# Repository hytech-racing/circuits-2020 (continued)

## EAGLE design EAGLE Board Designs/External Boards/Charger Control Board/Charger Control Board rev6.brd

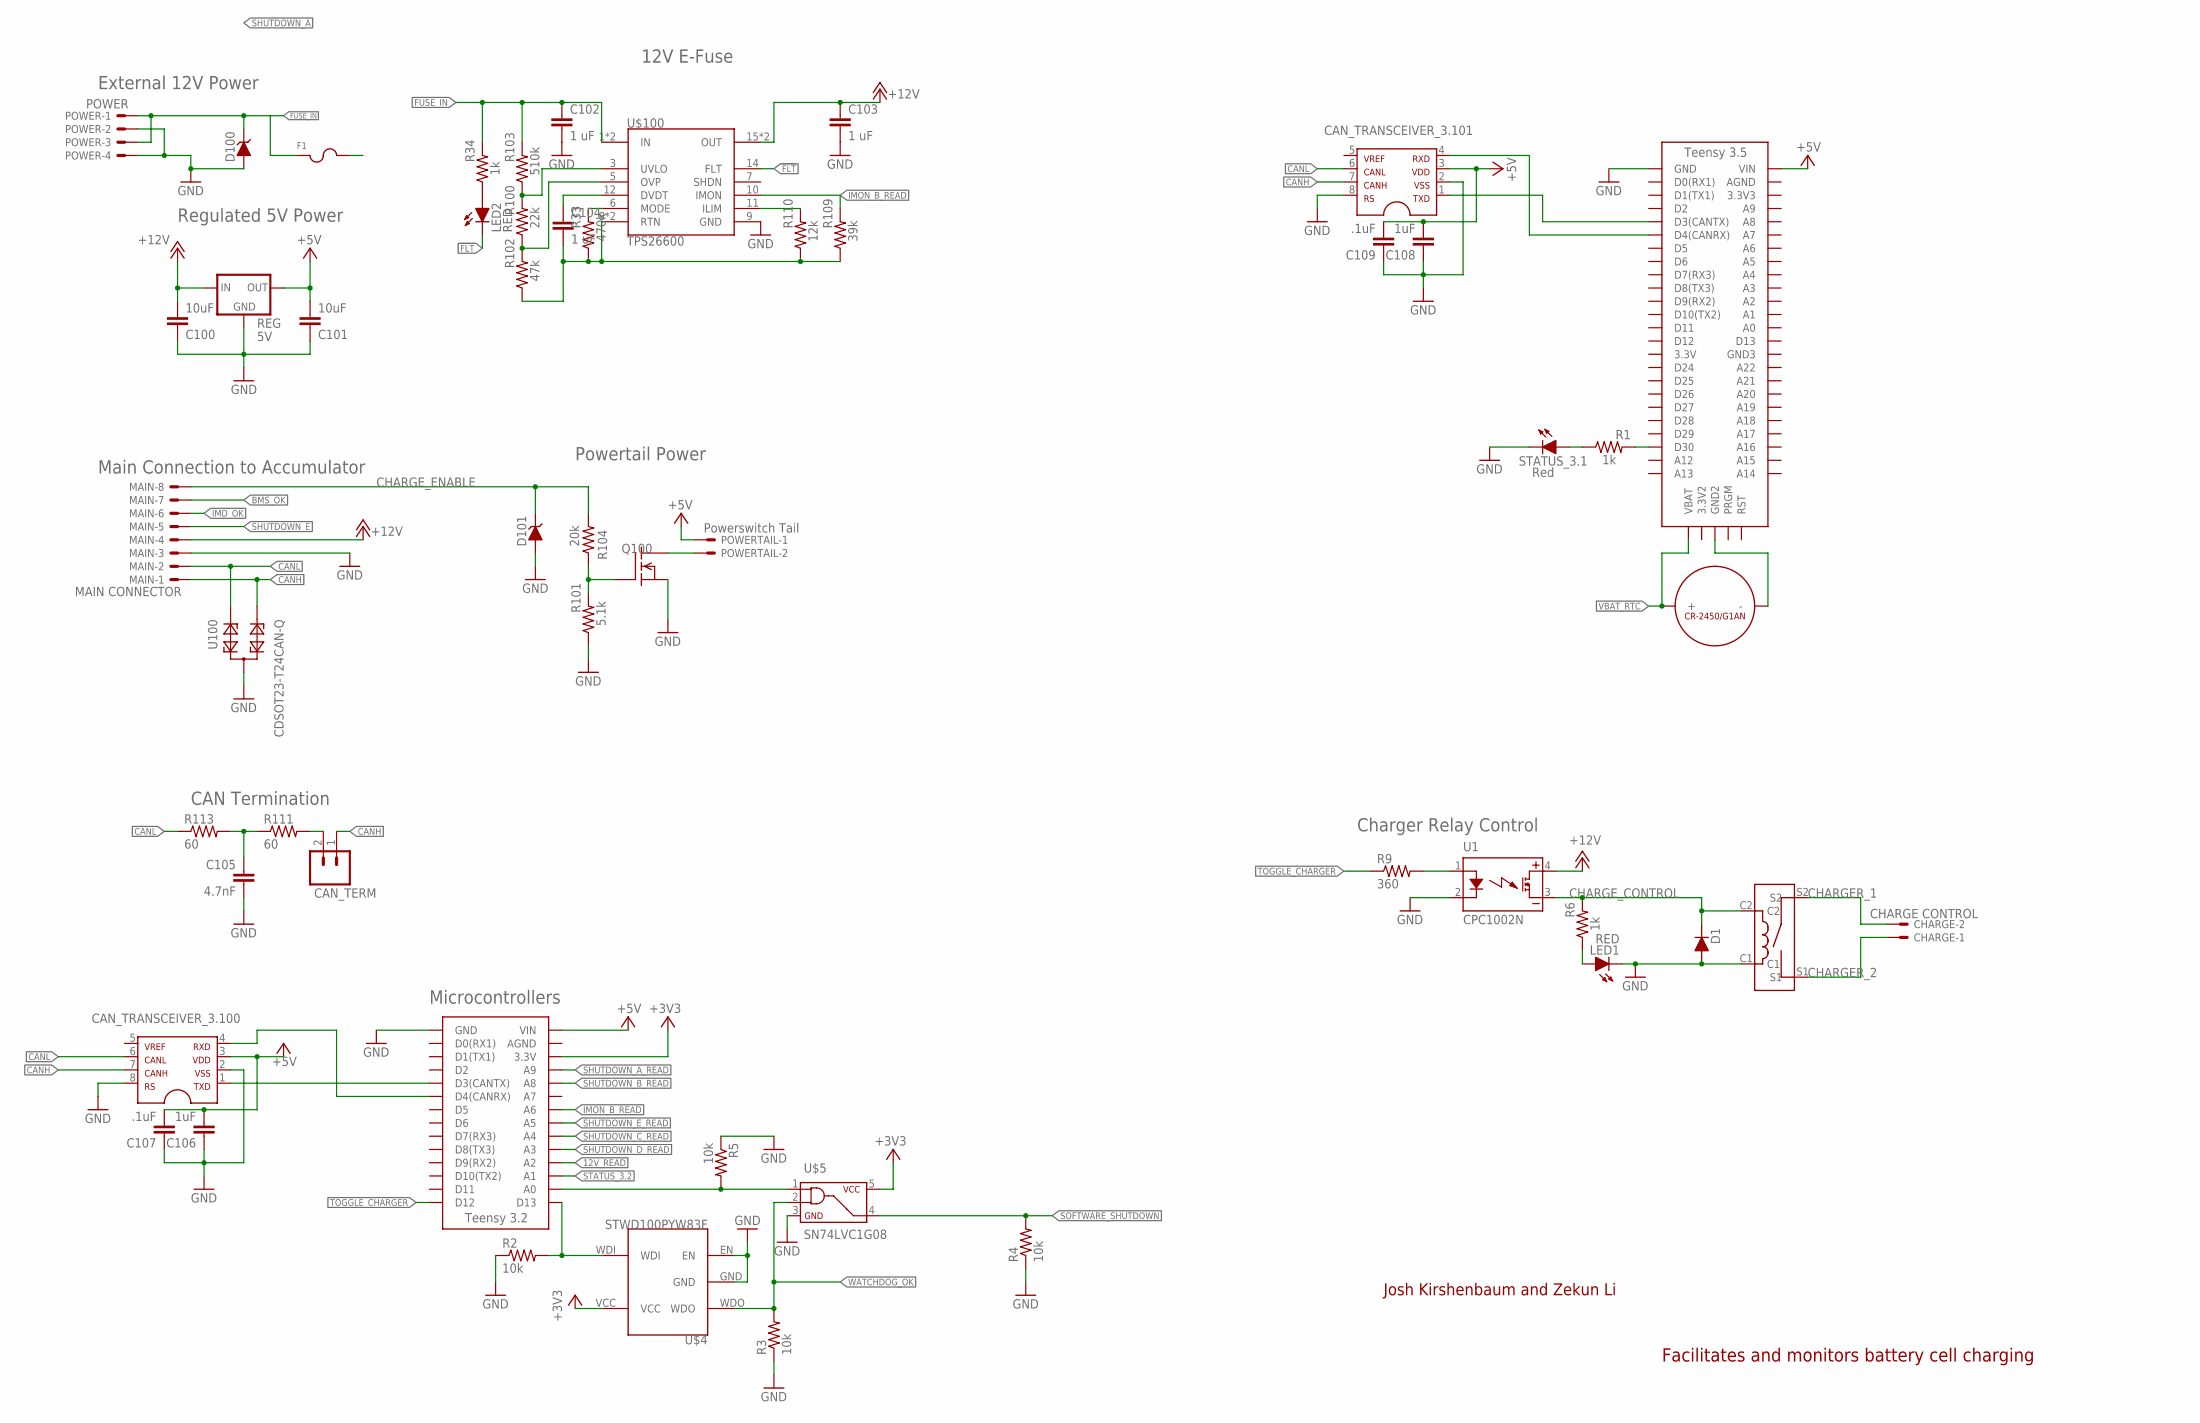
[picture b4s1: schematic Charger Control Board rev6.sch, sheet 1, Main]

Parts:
$$$$U$100: CR-2450/G1AN
$$U$6: TEENSY_3.2_SIMPLE
$$U$7: KT12-1A-40L-THT
C100: 10uF; 0603-CAP; TOLERANCE 1%; VOLTAGE 25V
C101: 10uF; 0603-CAP; TOLERANCE 5%; VOLTAGE 25V
C102, C103, C104: 1 uF; 0603-CAP
C105: 4.7nF; 0603-CAP; TOLERANCE 5%; VOLTAGE 50V
C106, C108: 1uF; 0603-CAP; TOLERANCE 5%; VOLTAGE 10V
C107, C109: .1uF; 0603-CAP; TOLERANCE 5%; VOLTAGE 10V
CAN_TERM: M02_SLIM; 1X02_SLIM
CAN_TRANSCEIVER_3.100, CAN_TRANSCEIVER_3.101: MCP2551; SOIC-08
CHARGE: CHARGE CONTROL; NANO-FIT_VERTICAL-2
D1: DIODE; 0805_D
D100: DIODE_ZENER0603; 0603_D
D101: DIODE_ZENER; SOT23
F1: FUSE_MINIBLADE; MINI-BLADE_FUSE_HOLDER
LED1, LED2: RED; LED-603
MAIN: MAIN CONNECTOR; NANO-FIT_VERTICAL-8
POWER: POWER; NANO-FIT_VERTICAL-4
POWERTAIL: Powerswitch Tail; NANO-FIT_VERTICAL-2
Q100: DMG3406LSOT; SOT23
R1, R6, R34: 1k; 0603-RES; TOLERANCE 1%
R2, R3, R4, R5: 10k; 0603-RES
R9: 360; 0603-RES; TOLERANCE 1%
R33: 470k; 0603-RES; TOLERANCE 1%
R100: 22k; 0603-RES; TOLERANCE 1%
R101: 5.1k; 0603-RES; TOLERANCE 1%
R102: 47k; 0603-RES; TOLERANCE 1%
R103: 510k; 0603-RES; TOLERANCE 1%
R104: 20k; 0603-RES; TOLERANCE 1%
R109: 39k; 0603-RES; TOLERANCE 1%
R110: 12k; 0603-RES; TOLERANCE 1%
R111, R113: 60; 0603-RES; TOLERANCE 1%
REG: 5V; OKI-78SR
STATUS_3.1: Red; LED-603
U1: CPC1002N; SOP04
U100: CDSOT23-T24CAN-Q; SOT23
U$3: TEENSY_3.5_EXT_RTC
U$4: STWD100PYW83F; SOT323-5
U$5: SN74LVC1G08; SOT-23-5
U$100: TPS26600; HTSSOP-16

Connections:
12V_READ: $$U$6.A2; also elsewhere on the board
!FLT!: LED2.C, U$100.14 (FLT)
+3V3: $$U$6.3.3V, U$4.VCC, U$5.5
+5V: $$U$6.VIN, C101.2, C106.2, C107.2, C108.2, C109.2, CAN_TRANSCEIVER_3.100.3, CAN_TRANSCEIVER_3.101.3, POWERTAIL.P$1, REG.3 (OUT), U$3.VIN; also elsewhere on the board
+12V: C100.2, C103.1, MAIN.P$4, REG.1 (IN), U1.4 (DC+), U$100.15 (OUT), U$100.16 (OUT); also elsewhere on the board
BMS_OK: MAIN.P$7; also elsewhere on the board
CANH: CAN_TERM.1, CAN_TRANSCEIVER_3.100.7, CAN_TRANSCEIVER_3.101.7, MAIN.P$1, U100.2
CANL: CAN_TRANSCEIVER_3.100.6, CAN_TRANSCEIVER_3.101.6, MAIN.P$2, R113.1, U100.1
CHARGER_1: $$U$7.S1, CHARGE.P$1
CHARGER_2: $$U$7.S2, CHARGE.P$2
CHARGE_CONTROL: $$U$7.C2, D1.C, R6.2, U1.3 (DC-)
CHARGE_ENABLE: D101.3 (C), MAIN.P$8, R104.2
DVDT_A: C104.1, U$100.12 (DVDT)
FUSE_IN: C102.1, D100.C, F1.L1 (1), F1.L2 (1), POWER.P$1, POWER.P$3, R34.2, R103.2, U$100.1 (IN), U$100.2 (IN)
GND: $$U$6.GND, $$U$7.C1, C100.1, C101.1, C102.2, C103.2, C105.2, C106.1, C107.1, C108.1, C109.1, CAN_TRANSCEIVER_3.100.2, CAN_TRANSCEIVER_3.100.8, CAN_TRANSCEIVER_3.101.2, CAN_TRANSCEIVER_3.101.8, D1.A, D100.A, D101.1 (A), LED1.C, MAIN.P$3, POWER.P$2, POWER.P$4, Q100.2 (S), R2.1, R3.1, R4.1, R5.1, R101.1, REG.2 (GND), STATUS_3.1.C, U1.2 (CONTROL-), U100.3, U$3.GND, U$4.EN, U$4.GND, U$5.3, U$100.9 (GND); also elsewhere on the board
ILIM_A: R110.2, U$100.11 (ILIM)
IMD_OK: MAIN.P$6; also elsewhere on the board
IMON_B_READ: $$U$6.A6, R109.2, U$100.10 (IMON)
unnamed: POWERTAIL.P$2, Q100.3 (D)
unnamed: CAN_TRANSCEIVER_3.101.4, U$3.D4(CANRX)
unnamed: Q100.1 (G), R101.2, R104.1
unnamed: CAN_TRANSCEIVER_3.101.1, U$3.D3(CANTX)
unnamed: R1.1, STATUS_3.1.A
unnamed: R1.2, U$3.D30
unnamed: R9.2, U1.1 (CONTROL+)
unnamed: $$U$6.A0, R5.2, U$5.1
unnamed: $$U$6.D4(CANRX), CAN_TRANSCEIVER_3.100.4
unnamed: $$U$6.D13, R2.2, U$4.WDI
unnamed: CAN_TERM.2, R111.2
unnamed: $$U$6.D3(CANTX), CAN_TRANSCEIVER_3.100.1
unnamed: R33.2, U$100.6 (MODE)
unnamed: LED2.A, R34.1
unnamed: LED1.A, R6.1
unnamed: $$$$U$100.-, U$3.GND2
unnamed: C105.1, R111.1, R113.2
OVP_A: R100.1, R102.2, U$100.5 (OVP)
RTN_A: C104.2, R33.1, R102.1, R109.1, R110.1, U$100.8 (RTN), U$100.PAD (RTN)
SHUTDOWN_A: F1.R1 (2), F1.R2 (2); also elsewhere on the board
SHUTDOWN_A_READ: $$U$6.A9; also elsewhere on the board
SHUTDOWN_B_READ: $$U$6.A8; also elsewhere on the board
SHUTDOWN_C_READ: $$U$6.A4; also elsewhere on the board
SHUTDOWN_D_READ: $$U$6.A3; also elsewhere on the board
SHUTDOWN_E: MAIN.P$5; also elsewhere on the board
SHUTDOWN_E_READ: $$U$6.A5; also elsewhere on the board
SOFTWARE_SHUTDOWN: R4.2, U$5.4; also elsewhere on the board
STATUS_3.2: $$U$6.A1; also elsewhere on the board
TOGGLE_CHARGER: $$U$6.D12, R9.1
UVLO_A: R100.2, R103.1, U$100.3 (UVLO)
VBAT_RTC: $$$$U$100.+_0 (+), $$$$U$100.+_1 (+), U$3.VBAT
WATCHDOG_OK: R3.2, U$4.WDO, U$5.2; also elsewhere on the board

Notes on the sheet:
Main Connection to Accumulator
Powertail Power
Charger Relay Control
CAN Termination
Microcontrollers
External 12V Power
Regulated 5V Power
Josh Kirshenbaum and Zekun Li
Facilitates and monitors battery cell charging
12V E-Fuse

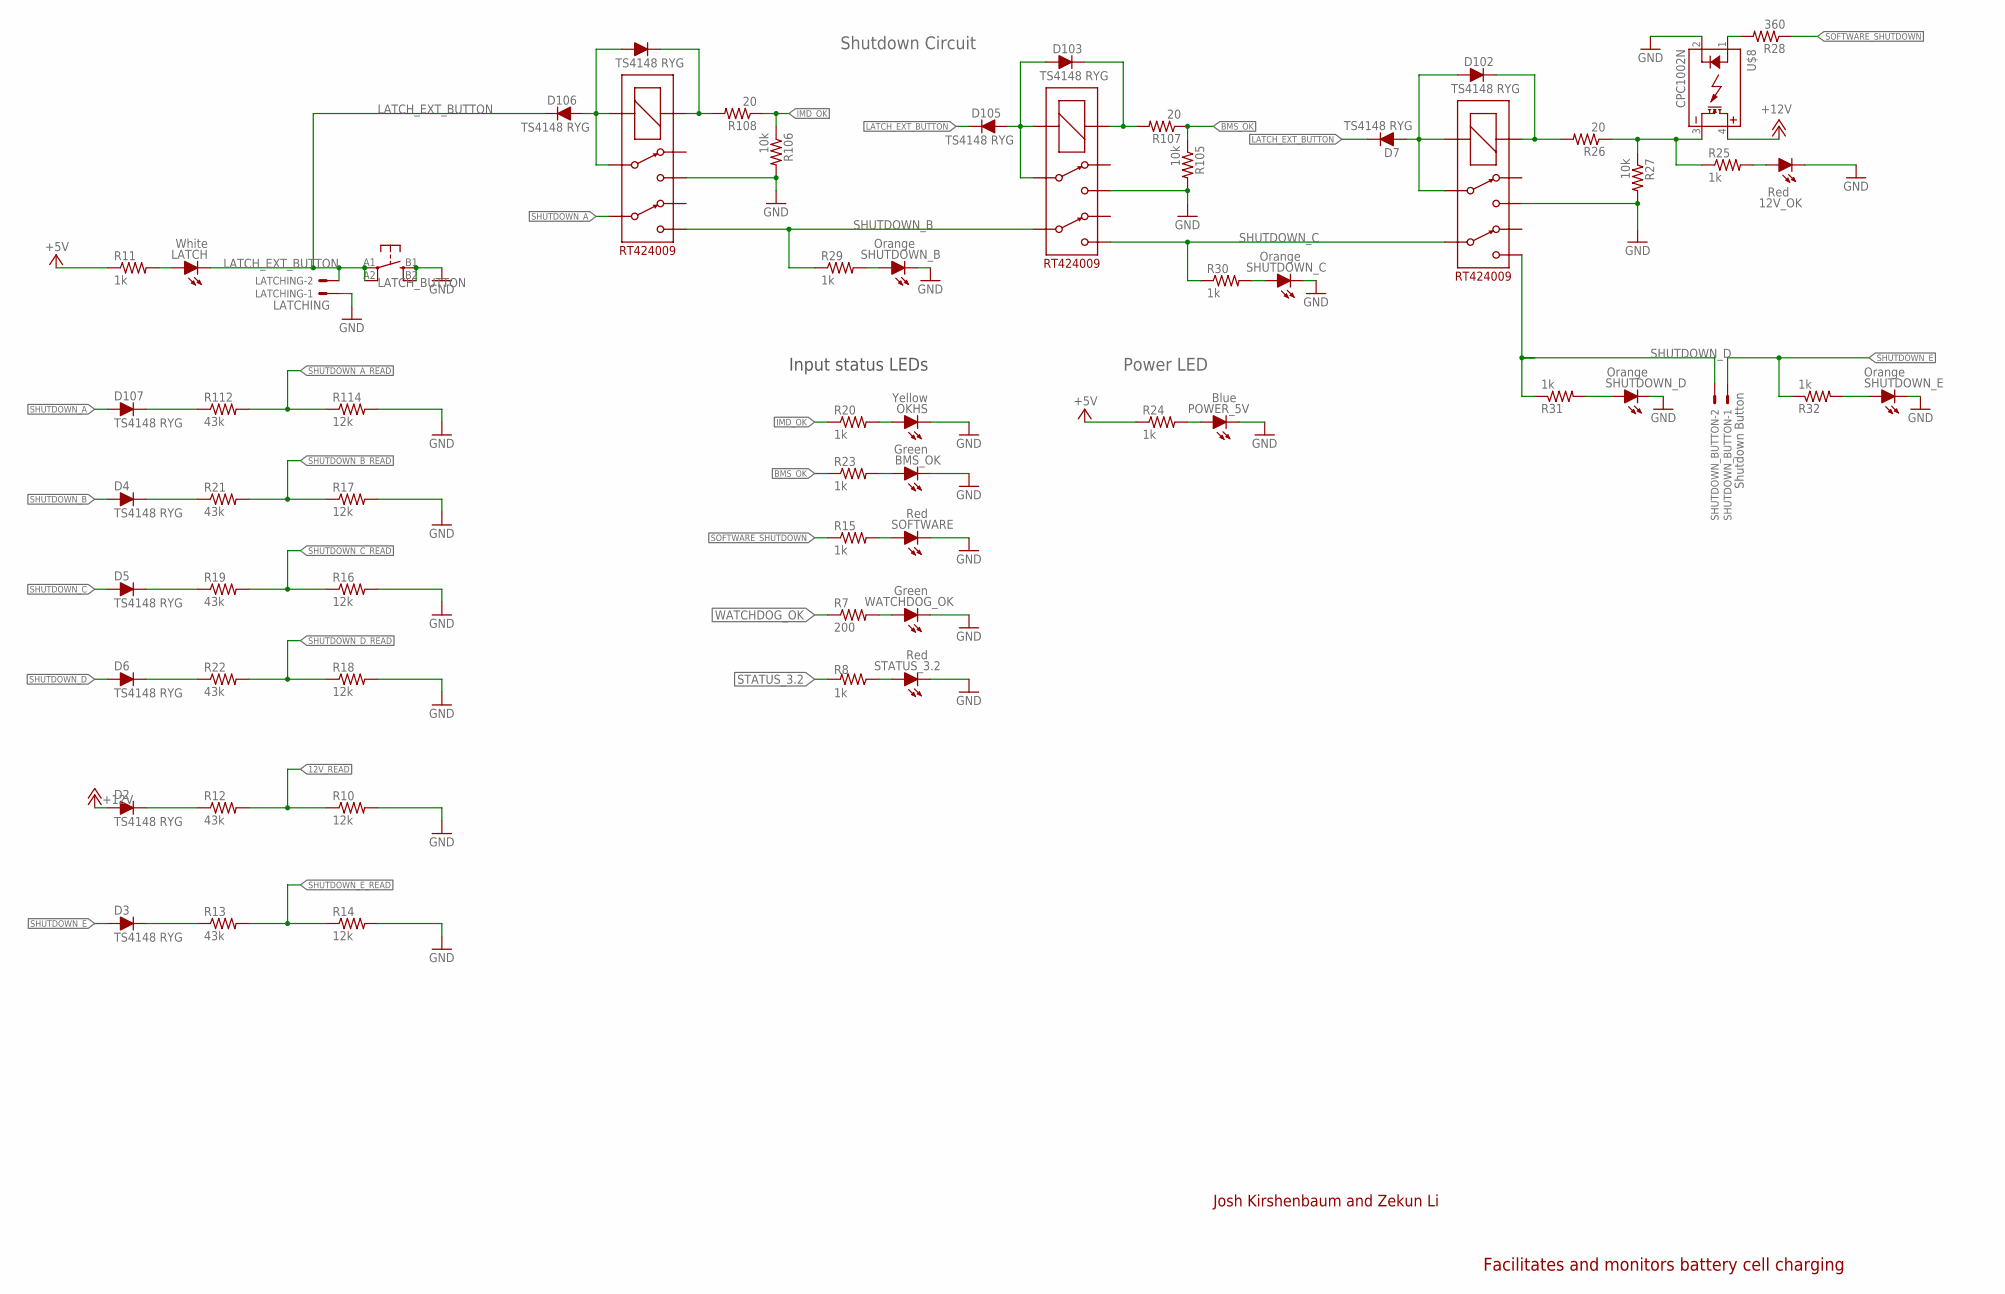
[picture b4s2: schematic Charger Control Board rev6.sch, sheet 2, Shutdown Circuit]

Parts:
12V_OK: Red; LED-603
BMS_OK: Green; LED-603
BMS_SHUTDOWN_RLY, BMS_SHUTDOWN_RLY1: RT424009; RELAY_DPDT
D2, D3, D4, D5, D6, D7, D102, D103, D104, D105, D106, D107: TS4148 RYG; 0805_D
IMD_SHUTDOWN_RLY: RT424009; RELAY_DPDT
LATCH: White; LED-603
LATCHING: LATCHING; NANO-FIT_VERTICAL-2
LATCH_BUTTON: BTN_10-XXSMD; TACTILE_SWITCH_SMD_6.2MM_TALL
OKHS: Yellow; LED-603
POWER_5V: Blue; LED-603
R7: 200; 0603-RES
R8, R11, R20, R23, R24, R25, R29, R30: 1k; 0603-RES; TOLERANCE 1%
R10, R14, R16, R17, R18, R114: 12k; 0603-RES
R12, R13, R19, R21, R22, R112: 43k; 0603-RES
R15, R31, R32: 1k; 0603-RES
R26, R107, R108: 20; 0603-RES; TOLERANCE 1%
R27: 10k; 0603-RES
R28: 360; 0603-RES; TOLERANCE 1%
R105, R106: 10k; 0603-RES; TOLERANCE 1%
SHUTDOWN_B: Orange; LED-603
SHUTDOWN_BUTTON: Shutdown Button; NANO-FIT_VERTICAL-2
SHUTDOWN_C: Orange; LED-603
SHUTDOWN_D: Orange; LED-603
SHUTDOWN_E: Orange; LED-603
SOFTWARE: Red; LED-603
STATUS_3.2: Red; LED-603
U$8: CPC1002N; SOP04
WATCHDOG_OK: Green; LED-603

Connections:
12V_READ: R10.1, R12.2; also elsewhere on the board
+5V: R11.1, R24.1; also elsewhere on the board
+12V: D2.A, U$8.4 (DC+); also elsewhere on the board
BMS_OK: R23.1, R105.1, R107.1; also elsewhere on the board
BMS_OK_RELAY: BMS_SHUTDOWN_RLY.COIL+, D103.C, R107.2
BMS_PWR_STEP: BMS_SHUTDOWN_RLY.3, BMS_SHUTDOWN_RLY.COIL-, D103.A, D105.A
GND: 12V_OK.C, BMS_OK.C, BMS_SHUTDOWN_RLY.4, BMS_SHUTDOWN_RLY1.4, IMD_SHUTDOWN_RLY.4, LATCHING.P$1, LATCH_BUTTON.B1 (S), LATCH_BUTTON.B2 (S1), OKHS.C, POWER_5V.C, R10.2, R14.2, R16.2, R17.2, R18.2, R27.2, R105.2, R106.2, R114.2, SHUTDOWN_B.C, SHUTDOWN_C.C, SHUTDOWN_D.C, SHUTDOWN_E.C, SOFTWARE.C, STATUS_3.2.C, U$8.2 (CONTROL-), WATCHDOG_OK.C; also elsewhere on the board
IMD_OK: R20.1, R106.1, R108.1; also elsewhere on the board
IMD_PWR_STEP: D104.A, D106.A, IMD_SHUTDOWN_RLY.3, IMD_SHUTDOWN_RLY.COIL-
LATCH_EXT_BUTTON: D7.C, D105.C, D106.C, LATCH.C, LATCHING.P$2, LATCH_BUTTON.A1, LATCH_BUTTON.A2 (P1)
unnamed: LATCH.A, R11.2
unnamed: BMS_OK.A, R23.2
unnamed: R8.1, STATUS_3.2.A
unnamed: D104.C, IMD_SHUTDOWN_RLY.COIL+, R108.2
unnamed: R25.1, R26.1, R27.1, U$8.3 (DC-)
unnamed: D107.C, R112.1
unnamed: D4.C, R21.1
unnamed: R29.2, SHUTDOWN_B.A
unnamed: D5.C, R19.1
unnamed: D6.C, R22.1
unnamed: BMS_SHUTDOWN_RLY1.3, BMS_SHUTDOWN_RLY1.COIL-, D7.A, D102.A
unnamed: R7.2, WATCHDOG_OK.A
unnamed: POWER_5V.A, R24.2
unnamed: OKHS.A, R20.2
unnamed: R28.2, U$8.1 (CONTROL+)
unnamed: D3.C, R13.1
unnamed: R32.2, SHUTDOWN_E.A
unnamed: R31.2, SHUTDOWN_D.A
unnamed: R15.2, SOFTWARE.A
unnamed: R30.2, SHUTDOWN_C.A
unnamed: BMS_SHUTDOWN_RLY1.COIL+, D102.C, R26.2
unnamed: 12V_OK.A, R25.2
unnamed: D2.C, R12.1
SHUTDOWN_A: D107.A, IMD_SHUTDOWN_RLY.6; also elsewhere on the board
SHUTDOWN_A_READ: R112.2, R114.1; also elsewhere on the board
SHUTDOWN_B: BMS_SHUTDOWN_RLY.6, D4.A, IMD_SHUTDOWN_RLY.5, R29.1
SHUTDOWN_B_READ: R17.1, R21.2; also elsewhere on the board
SHUTDOWN_C: BMS_SHUTDOWN_RLY.5, BMS_SHUTDOWN_RLY1.6, D5.A, R30.1
SHUTDOWN_C_READ: R16.1, R19.2; also elsewhere on the board
SHUTDOWN_D: BMS_SHUTDOWN_RLY1.5, D6.A, R31.1, SHUTDOWN_BUTTON.P$2
SHUTDOWN_D_READ: R18.1, R22.2; also elsewhere on the board
SHUTDOWN_E: D3.A, R32.1, SHUTDOWN_BUTTON.P$1; also elsewhere on the board
SHUTDOWN_E_READ: R13.2, R14.1; also elsewhere on the board
SOFTWARE_SHUTDOWN: R15.1, R28.1; also elsewhere on the board
STATUS_3.2: R8.2; also elsewhere on the board
WATCHDOG_OK: R7.1; also elsewhere on the board

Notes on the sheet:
Shutdown Circuit
Input status LEDs
Power LED
Josh Kirshenbaum and Zekun Li
Facilitates and monitors battery cell charging

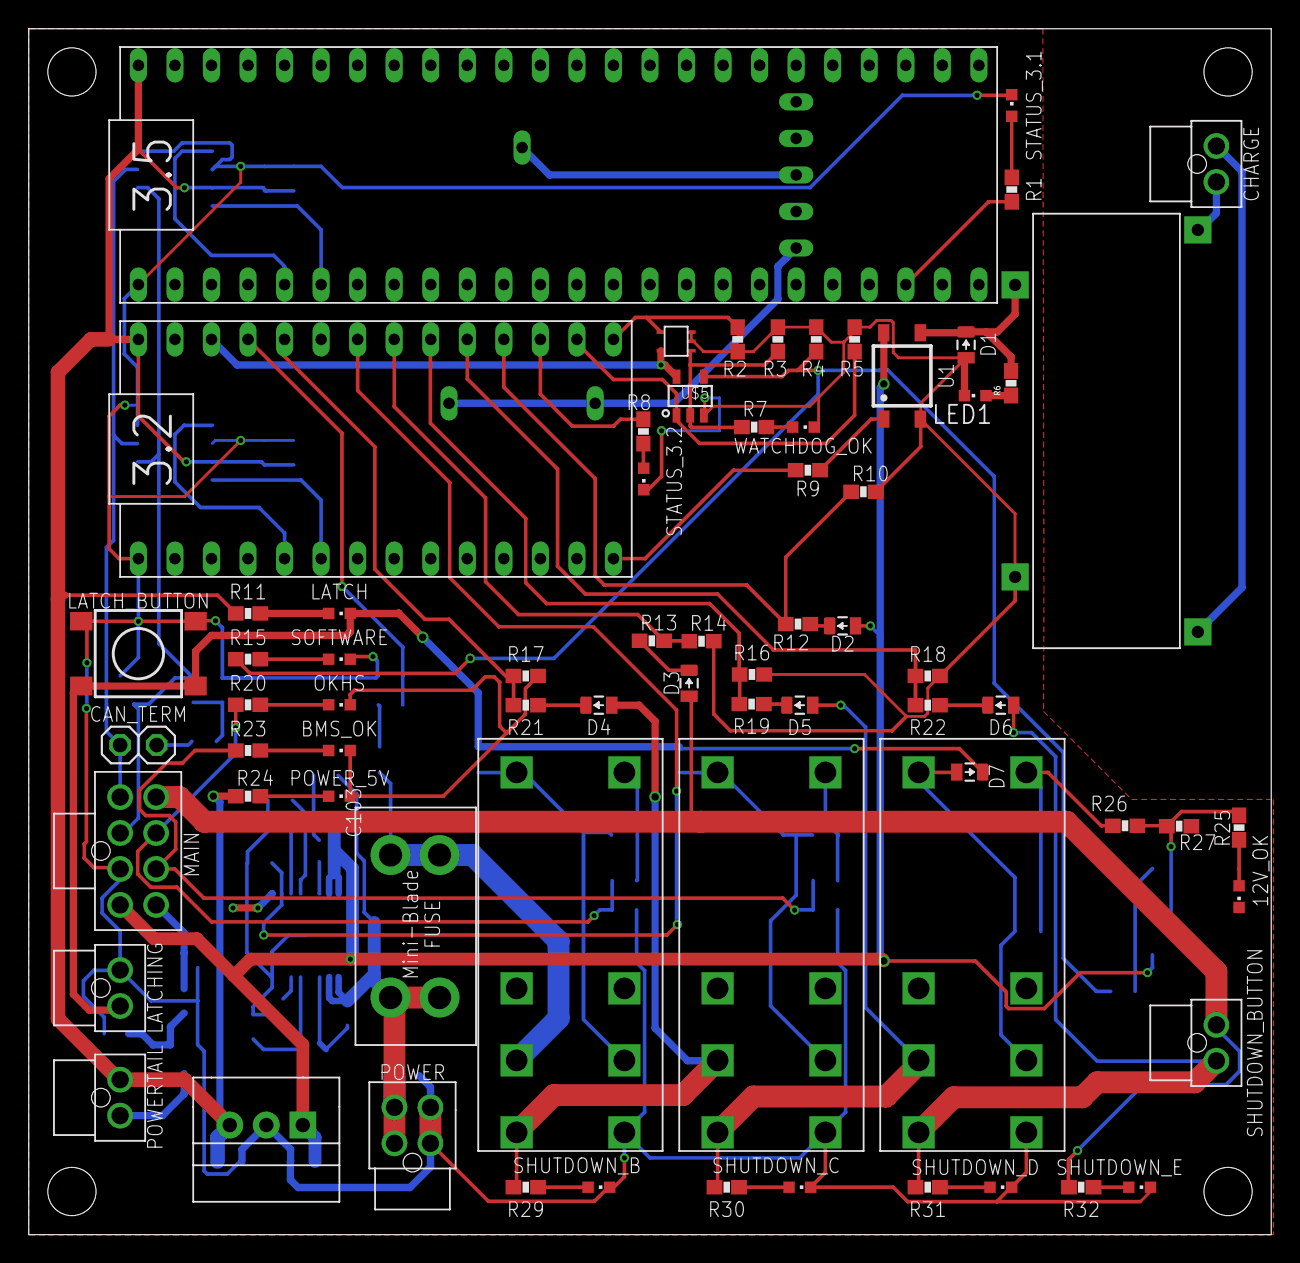
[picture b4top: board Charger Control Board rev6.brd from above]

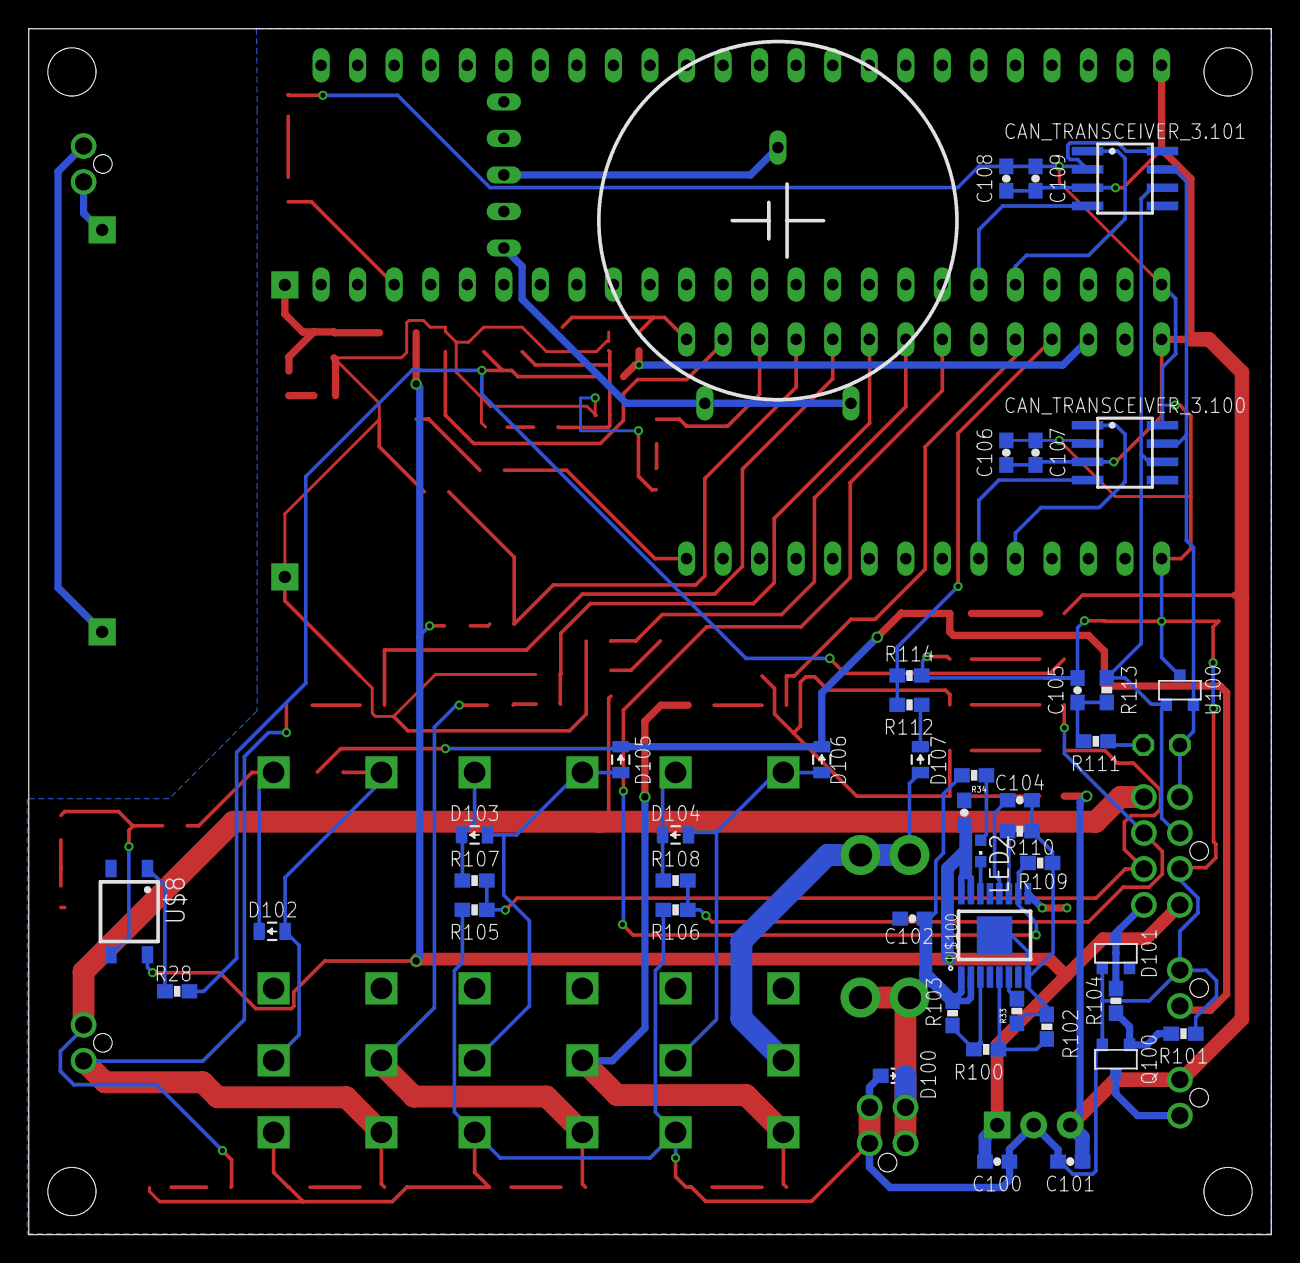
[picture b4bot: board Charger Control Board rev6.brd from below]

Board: 2 copper layers, 86.4 x 83.8 mm, 119 parts (44 on the bottom side), 80 nets.

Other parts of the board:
$$U$1, $$U$2: M3_MOUNTING
U$1, U$2: M3_MOUNTING

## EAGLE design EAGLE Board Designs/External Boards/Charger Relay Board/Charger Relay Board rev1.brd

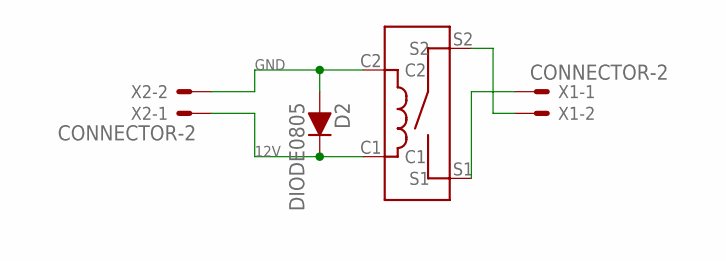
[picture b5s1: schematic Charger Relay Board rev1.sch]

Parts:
D2: DIODE0805; 0805_D
U$1: KT12-1A-40L-THT
X1, X2: CONNECTOR-2; MINIFIT_5566-2

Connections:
12V: D2.C, U$1.C1, X2.1
GND: D2.A, U$1.C2, X2.2
unnamed: U$1.S2, X1.2
unnamed: U$1.S1, X1.1

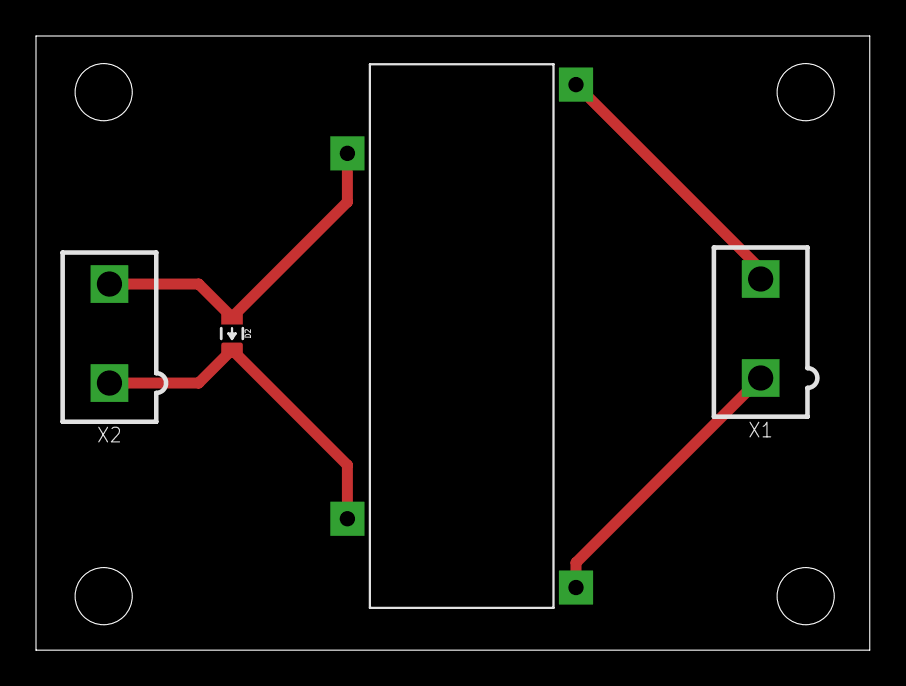
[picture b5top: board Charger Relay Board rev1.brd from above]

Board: 2 copper layers, 46.3 x 34.1 mm, 4 parts (0 on the bottom side), 4 nets.

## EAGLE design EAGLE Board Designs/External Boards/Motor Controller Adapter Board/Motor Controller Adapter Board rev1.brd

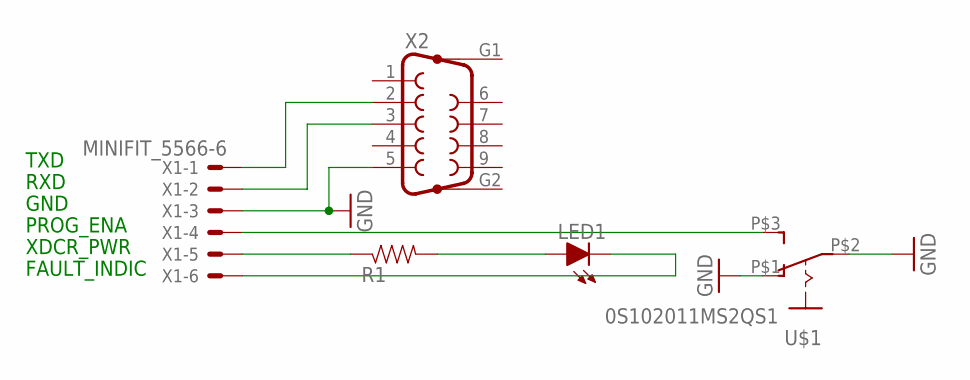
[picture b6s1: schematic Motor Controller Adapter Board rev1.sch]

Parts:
LED1: LED-0805; LED-805
R1: RESISTOR0805-RES; 0805
U$1: 0S102011MS2QS1
X1: MINIFIT_5566-6
X2: F09HP

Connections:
GND: U$1.P$1 (O), U$1.P$2, X1.3, X2.5
unnamed: LED1.A, R1.2
unnamed: R1.1, X1.5
unnamed: LED1.C, X1.6
unnamed: U$1.P$3 (S), X1.4
unnamed: X1.1, X2.2
unnamed: X1.2, X2.3

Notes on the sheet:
TXD
RXD
GND
PROG_ENA
XDCR_PWR
FAULT_INDIC

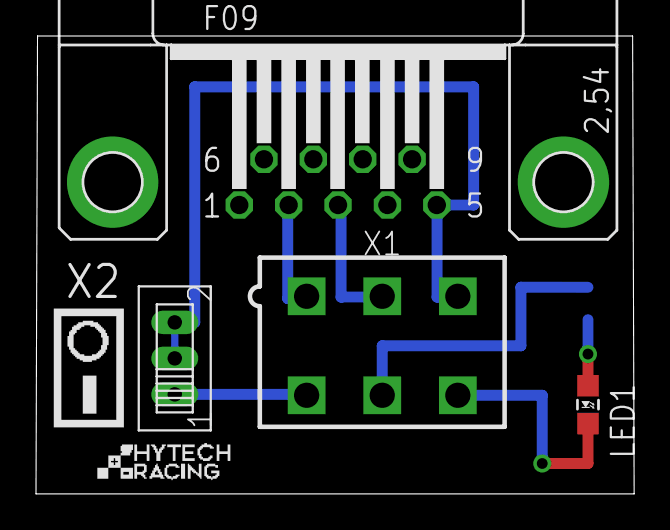
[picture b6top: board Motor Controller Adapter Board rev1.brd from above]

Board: 2 copper layers, 33.2 x 25.4 mm, 5 parts (1 on the bottom side), 7 nets.
